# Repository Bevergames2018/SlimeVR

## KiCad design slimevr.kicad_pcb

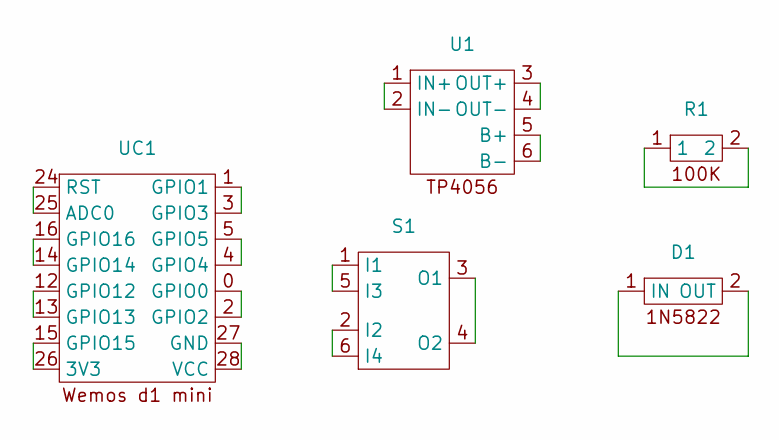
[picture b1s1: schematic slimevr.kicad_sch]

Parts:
D1: D_1N5822
R1: R_100k
S1: switch_aliexpress
U1: TP4056
UC1: wemos_d1_mini_v4

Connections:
unnamed: D1.1 (IN), D1.2 (OUT)
unnamed: R1.1, R1.2
unnamed: S1.1 (I1), S1.5 (I3)
unnamed: S1.2 (I2), S1.6 (I4)
unnamed: S1.3 (O1), S1.4 (O2)
unnamed: U1.5 (B+), U1.6 (B-)
unnamed: U1.1 (IN+), U1.2 (IN-)
unnamed: U1.3 (OUT+), U1.4 (OUT-)
unnamed: UC1.15 (GPIO15), UC1.26 (3V3)
unnamed: UC1.24 (RST), UC1.25 (ADC0)
unnamed: UC1.27 (GND), UC1.28 (VCC)
unnamed: UC1.0 (GPIO0), UC1.2 (GPIO2)
unnamed: UC1.1 (GPIO1), UC1.3 (GPIO3)
unnamed: UC1.4 (GPIO4), UC1.5 (GPIO5)
unnamed: UC1.12 (GPIO12), UC1.13 (GPIO13)
unnamed: UC1.14 (GPIO14), UC1.16 (GPIO16)

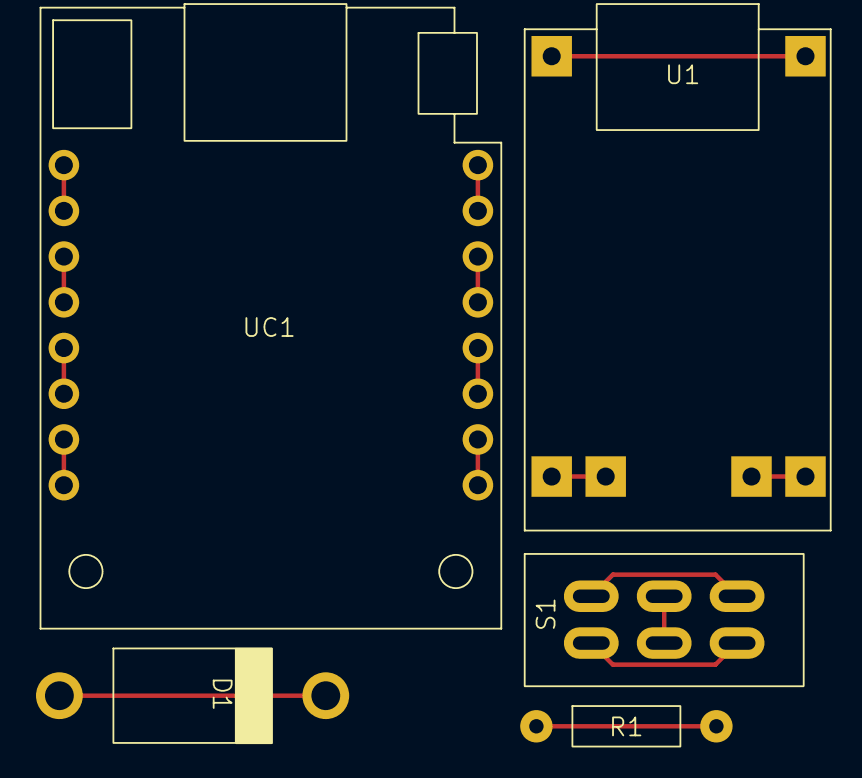
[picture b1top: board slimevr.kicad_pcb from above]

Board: 2 copper layers, 5 parts (0 on the bottom side), 16 nets.

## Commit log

2023-11-20 First upload
